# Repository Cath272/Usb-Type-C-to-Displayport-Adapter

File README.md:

# Usb Type C to Displayport Adapter
 Usb Type C (DP Alt Mode)  to Displayport Adapter
 4 DP lanes

 Simple Usb C to Displayport Adapter using the VL100-Q3/VL103-Q3 ic
 VL103-Q3 does not need external crystal but VL100-Q3 can be found cheaper 

 The design is not final!

 ## VL100-Q3/VL103-Q3

  - CC Logic & PD 3.0 Engine 

  - Compliant to VESA DisplayPort Alt Mode on USB Type C Standard Version 1.0 a

  - USB Billboard Device

  ###  Built-in Voltage Regulators

- 5.0V to 3.3V LDO

- 3.3V to 1.8V LDO

## PCB 
This board uses a 4 layer stackup with a  1.6mm thickness:

- POWER/SIGNAL

- GND
  
- GND
  
- POWER/SIGNAL

High Speed diferential lines need a refrence ground plane so internal planes are ground referance planes for the High speed USB lines

### Schematic:

## PCB Screenshots

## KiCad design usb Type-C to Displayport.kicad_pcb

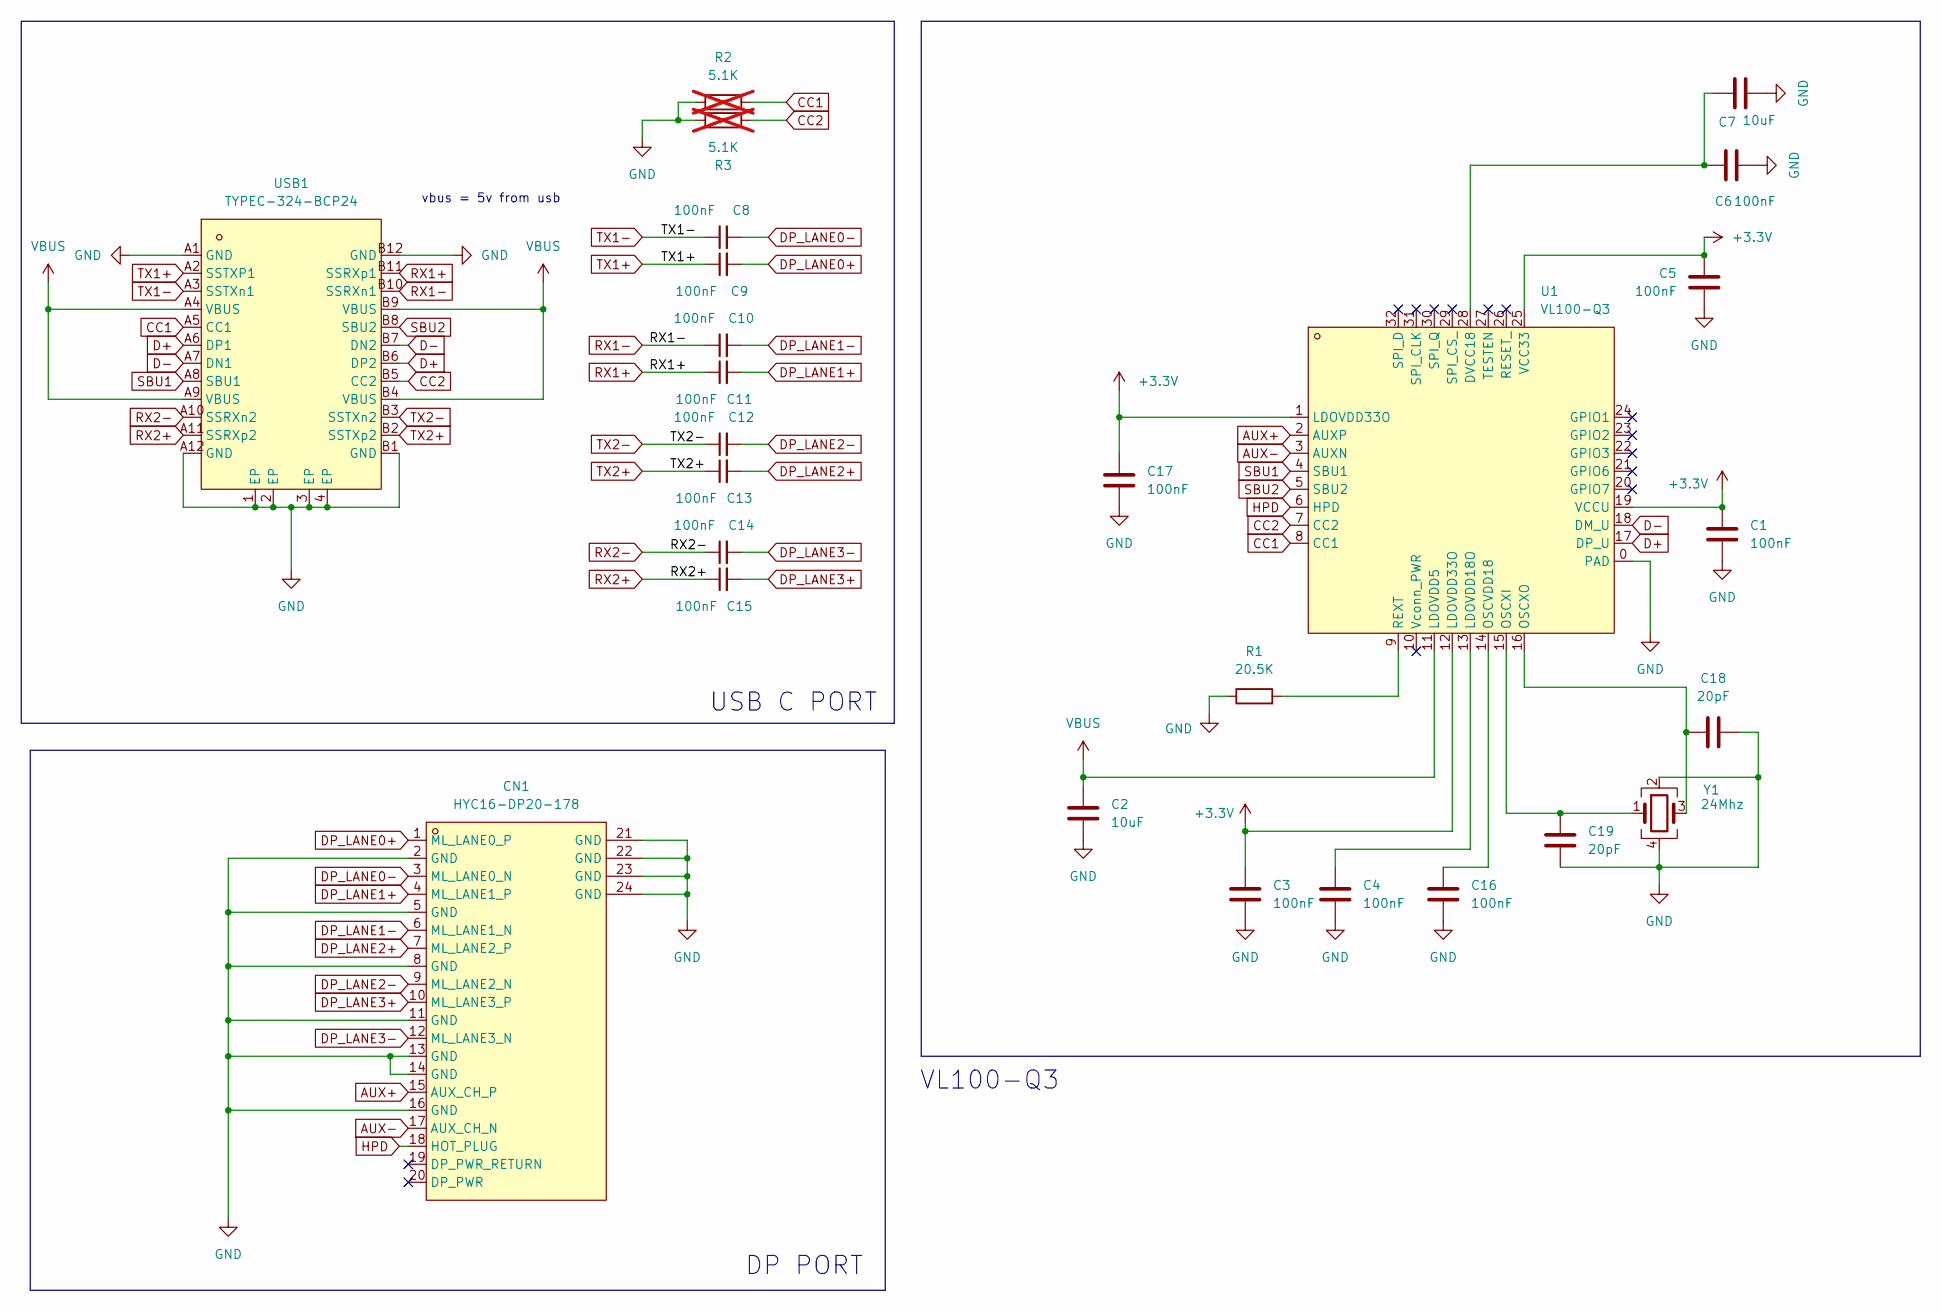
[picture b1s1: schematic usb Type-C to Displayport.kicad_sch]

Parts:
C1, C3, C4, C5, C6, C8, C9, C10, C11, C12, C13, C14, C15, C16, C17: 100nF; C_0402_1005Metric_Pad0.74x0.62mm_HandSolder
C2, C7: 10uF; C_0805_2012Metric_Pad1.18x1.45mm_HandSolder
C18, C19: 20pF; C_0402_1005Metric
CN1: HYC16-DP20-178; DP-SMD_HYC16-DP20-178; LCSC Part C711350
R1: 20.5K; R_0402_1005Metric_Pad0.72x0.64mm_HandSolder
R2, R3: 5.1K; R_0402_1005Metric; not fitted
U1: VL100-Q3; QFN-32_L5.0-W5.0-P0.50-BL-EP3.4; LCSC Part C69731
USB1: TYPEC-324-BCP24; USB-C-SMD_TYPEC-324-BCP24; LCSC Part C2835314
Y1: 24Mhz; Crystal_SMD_3225-4Pin_3.2x2.5mm

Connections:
+3.3V: C1.1, C3.1, C5.1, C17.1, U1.1 (LDOVDD33O), U1.12 (LDOVDD33O), U1.19 (VCCU), U1.25 (VCC33)
AUX+: CN1.15 (AUX_CH_P), U1.2 (AUXP)
AUX-: CN1.17 (AUX_CH_N), U1.3 (AUXN)
CC1: R2.1, U1.8 (CC1), USB1.A5 (CC1)
CC2: R3.1, U1.7 (CC2), USB1.B5 (CC2)
D+: U1.17 (DP_U), USB1.A6 (DP1), USB1.B6 (DP2)
D-: U1.18 (DM_U), USB1.A7 (DN1), USB1.B7 (DN2)
DP_LANE0+: C9.2, CN1.1 (ML_LANE0_P)
DP_LANE0-: C8.2, CN1.3 (ML_LANE0_N)
DP_LANE1+: C11.2, CN1.4 (ML_LANE1_P)
DP_LANE1-: C10.2, CN1.6 (ML_LANE1_N)
DP_LANE2+: C13.2, CN1.7 (ML_LANE2_P)
DP_LANE2-: C12.2, CN1.9 (ML_LANE2_N)
DP_LANE3+: C15.2, CN1.10 (ML_LANE3_P)
DP_LANE3-: C14.2, CN1.12 (ML_LANE3_N)
GND: C1.2, C2.2, C3.2, C4.2, C5.2, C6.2, C7.2, C16.2, C17.2, C18.2, C19.1, CN1.2 (GND), CN1.5 (GND), CN1.8 (GND), CN1.11 (GND), CN1.13 (GND), CN1.14 (GND), CN1.16 (GND), CN1.21 (GND), CN1.22 (GND), CN1.23 (GND), CN1.24 (GND), R1.1, R2.2, R3.2, U1.0 (PAD), USB1.1 (EP), USB1.2 (EP), USB1.3 (EP), USB1.4 (EP), USB1.A1 (GND), USB1.A12 (GND), USB1.B1 (GND), USB1.B12 (GND), Y1.2, Y1.4
HPD: CN1.18 (HOT_PLUG), U1.6 (HPD)
unnamed: C6.1, C7.1, U1.28 (DVCC18)
unnamed: C4.1, U1.13 (LDOVDD18O)
unnamed: C16.1, U1.14 (OSCVDD18)
unnamed: C19.2, U1.15 (OSCXI), Y1.1
unnamed: C18.1, U1.16 (OSCXO), Y1.3
unnamed: R1.2, U1.9 (REXT)
RX1+: C11.1, USB1.B11 (SSRXp1)
RX1-: C10.1, USB1.B10 (SSRXn1)
RX2+: C15.1, USB1.A11 (SSRXp2)
RX2-: C14.1, USB1.A10 (SSRXn2)
SBU1: U1.4 (SBU1), USB1.A8 (SBU1)
SBU2: U1.5 (SBU2), USB1.B8 (SBU2)
TX1+: C9.1, USB1.A2 (SSTXP1)
TX1-: C8.1, USB1.A3 (SSTXn1)
TX2+: C13.1, USB1.B2 (SSTXp2)
TX2-: C12.1, USB1.B3 (SSTXn2)
VBUS: C2.1, U1.11 (LDOVDD5), USB1.A4 (VBUS), USB1.A9 (VBUS), USB1.B4 (VBUS), USB1.B9 (VBUS)

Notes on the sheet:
vbus = 5v from usb
USB C PORT
VL100-Q3
DP PORT

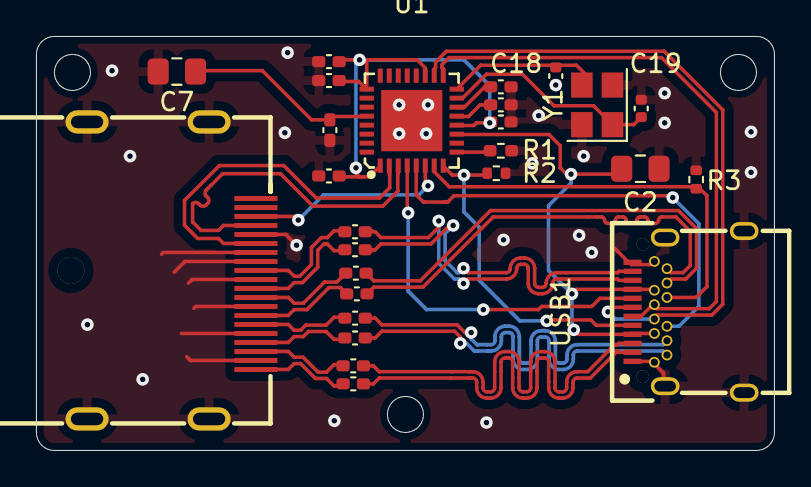
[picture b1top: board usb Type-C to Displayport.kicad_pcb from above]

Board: 4 copper layers, 41.0 x 23.0 mm, 26 parts (0 on the bottom side), 34 nets.

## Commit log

2025-02-07 Initial Release
    Uploaded Board, schematic and pics
2025-02-09 0.2
    Removed SPI chip, fixed CC lines being reversed, made pcb smaller, added mounting holes
2025-02-17 Changed IC to vl100 q3
    Changed ic to vl100 q3 (i found it cheaper and it's pin compatible, added Crystal)
2025-02-21 Fixed usb footprint
2025-02-22 Fixed DP lines
    Fixed wrong USB lines to DP lines, fixed differential pairs not length matched, length matched all 4 pairs
